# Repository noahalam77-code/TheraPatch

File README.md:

# TheraPatch

## Repository file structure
- BOM: JCLPCB BOM & regular BOM
- CADfiles: STEP files, STL files, and assembly notes
- PCB: PCB files, Gerber files, schematic images, and PCB images
- Firmware: Code & flashing instructions

## What it is
TheraPatch is a handheld therapeutic device designed to help mitigate the effects of injuries such as bruises, sprains, minor cuts, and more. By using a reverse-polarity system via an H-bridge, TheraPatch can heat the affected area (dilating blood vessels) or cool it (constricting blood vessels), both of which have been shown to help with injury healing at certain temperatures (which TheraPatch can achieve). 

## Motivation
I created TheraPatch with the primary motivation of helping people with common sports/activty related injuries while maintaining an efficient device to do so. Most of the time, when you have a bruise or scrape, you'd rely on disposable ice packs or inefficient heating pads, which are wasteful and time-consuming for long-term use. TheraPatch offers an effective, infinitely reusable solution to this. Instead of freezing water for 3-4 hours or boiling a heatpack everytime you need to reuse it, all you do with TheraPatch is plug and play. It's effective for athletes and normal people.

## Use of TheraPatch
To use the TheraPatch, first ensure your battery/wall adapter is plugged in. Then locate the 4 buttons on the top of the device; these buttons will allow you to set your desired parameters by moving through the menus: mode (hot/cold), set temp, and set time. After your desired settings are set, click the start button to initiate your therapy session, and place the side with the Peltier facing out against the affected area

## How it works
The TheraPatch looks like a simple black-and-white hot-cold block, but its guts are far more advanced. In electronics, generating heat is relatively simple. Electrons bump into each other rapidly in the wire, vibrating and thus creating the heat we feel. This is the easy part; cooling is the real engineering challenge. To cool it, I used a Peltier module, which transfers heat from one side to the other. Now, this needs to be driven by a heatsink and a fan to effectively cool. To achieve heating and cooling on the same side, I used an H bridge. The H-bridge module reverses the polarity in a Peltier module, meaning that when one side is positive and the other is negative, it cools; vice versa. All of this is controlled by a custom 4-layer PCB I designed in KiCad, with an ATmega328P as my microcontroller. The firmware reads a thermistor pressed against the Peltier plate and uses a bang-bang controller to turn the Peltier on/off to reach the desired temperature. This is all run by a rechargeable 12V battery, which charges via USB-C or a 12V wall adapter. These components are combined in a logical order in a CAD-designed box with a hole for all the input plugs and vent fans for air circulation.

Here are images of my project

## CAD with the PCB:

## CAD input ports, fins, and Peliter hole

## Link to Onshape case:

https://cad.onshape.com/documents/d627d659f05dae60588ec801/w/ad74ef98cd2d7a13cb59f9ec/e/f50ed022a94792dc2cfe6130?renderMode=0&uiState=6a4947abb17d022f5d41873a

# PCB (Signal Layer and ground):

## F.cu (signal traces and ground):

## In1.cu(ground):

## In2.cu (5V & 12V power)

## B.cu (signal traces and ground):

## 3D:

# Schematic (wiring diagram):

## Pic_1:

## Pwr:

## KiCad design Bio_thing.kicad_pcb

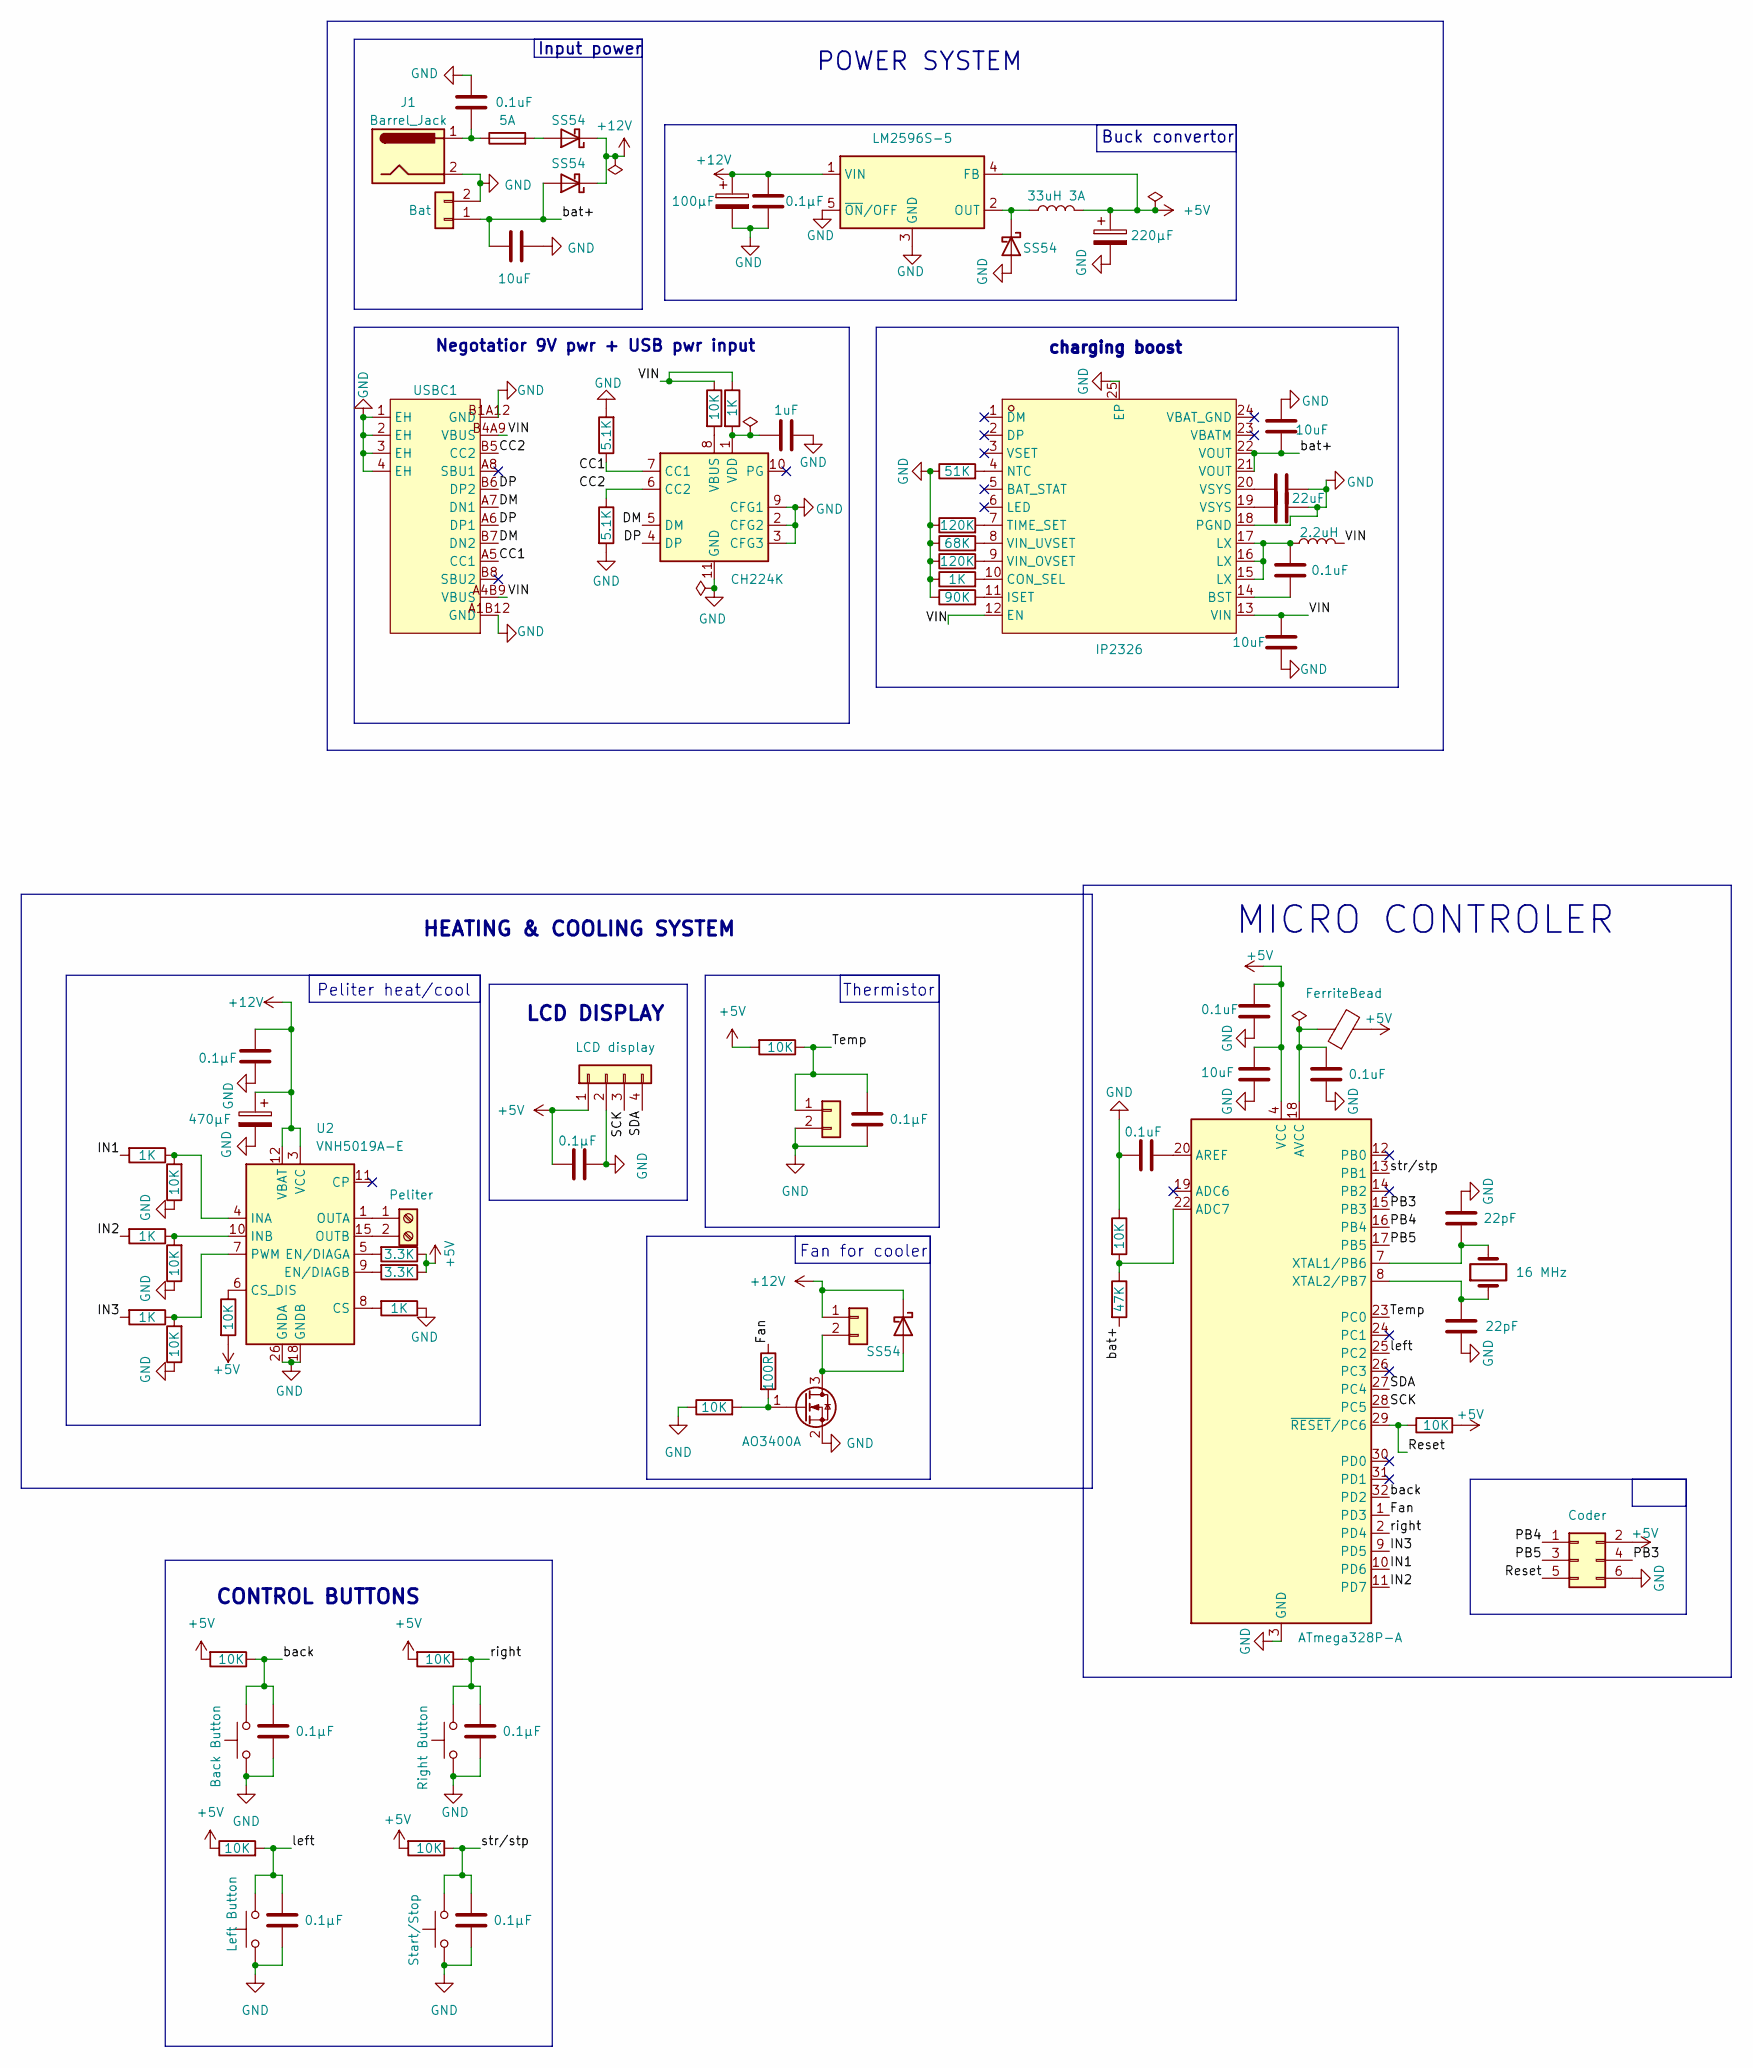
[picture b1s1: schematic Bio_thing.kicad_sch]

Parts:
C1, C3, C4, C5, C6, C9, C12, C15: 0.1µF; C_0603_1608Metric
C2: 220µF; CP_Elec_6.3x7.7
C7: 1uF; C_0603_1608Metric
C8: 100µF; CP_Elec_6.3x7.7
C10, C22, C23, C25: 10uF; C_1206_3216Metric
C11, C13, C18, C19, C24: 0.1uF; C_0603_1608Metric
C14, C17: 22uF; C_0805_2012Metric
C16: 470µF; CP_Elec_10x10.5
C20, C21: 22pF; C_0603_1608Metric
D1, D2, D3, D6: SS54; D_SMA
F2: 5A; Fuse_1206_3216Metric
FB1: FerriteBead; L_0805_2012Metric
J1: Barrel_Jack; Barrel_JJack
J2: Peliter; TerminalBlock_Phoenix_PT-1,5-2-5.0-H_1x02_P5.00mm_Horizontal
J4: Coder; PinHeader_2x03_P2.54mm_Vertical
J5: fan; JST_XH_B2B-XH-A_1x02_P2.50mm_Vertical
J6: LCD display; PinSocket_1x04_P2.54mm_Vertical
J7: Bat; JST_XH_B2B-XH-A_1x02_P2.50mm_Vertical
J9: themrisotorr; JST_XH_B2B-XH-A_1x02_P2.50mm_Vertical
L1: 33uH 3A; IND-SMD_L12.3-W12.3
L2: 2.2uH; L_Sunlord_MWSA0503S
Q4: AO3400A; SOT-23
R1, R2, R3, R5, R8, R9, R10, R12, R13, R16, R28, R33, R34: 10K; R_0805_2012Metric
R4, R6, R15, R17, R23, R32: 1K; R_0603_1608Metric
R7, R14: 3.3K; R_0603_1608Metric
R11: 100R; R_0603_1608Metric
R18, R19: 5.1K; R_0805_2012Metric
R20: 51K; R_0805_2012Metric
R21, R35: 120K; R_0805_2012Metric
R22: 68K; R_0805_2012Metric
R24: 90K; R_0805_2012Metric
R27: 47K; R_0805_2012Metric
SW2: Left Button; SW_PUSH_6mm_H4.3mm
SW3: Start/Stop; SW_PUSH_6mm_H4.3mm
SW4: Back Button; SW_PUSH_6mm_H4.3mm
SW5: Right Button; SW_PUSH_6mm_H4.3mm
U1: LM2596S-5; TO-263-5_TabPin3
U2: VNH5019A-E; ST_MultiPowerSO-30
U3: CH224K; ESSOP-10_L4.9-W3.9-P1.0-LS6.0-TL-EP
U4: ATmega328P-A; TQFP-32_7x7mm_P0.8mm
U5: IP2326; QFN-24-1EP_4x4mm_P0.5mm_EP2.6x2.6mm; MPN IP2326; LCSC Part C2832094
USBC1: TYPE-C-31-M-12; USB-C_SMD-TYPE-C-31-M-12_1; MPN TYPE-C-31-M-12; LCSC Part C165948
Y1: 16 MHz; Crystal_SMD_5032-2Pin_5.0x3.2mm

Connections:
+5V: C2.1, C12.1, C13.1, C22.1, FB1.2, J4.2, J6.1, L1.2, R2.2, R3.2, R5.2, R7.1, R8.2, R9.2, R10.1, R13.2, R14.1, U1.4 (FB), U4.4 (VCC), U4.6 (VCC)
+12V: C8.1, C9.1, C15.1, C16.1, D1.1 (K), D3.1 (K), D6.1 (K), J5.1, U1.1 (VIN), U2.3 (VCC), U2.12 (VBAT), U2.13 (VCC), U2.23 (VCC), U2.31 (VCC)
/CC1: R18.1, U3.7 (CC1), USBC1.A5 (CC1)
/CC2: R19.1, U3.6 (CC2), USBC1.B5 (CC2)
/DM: U3.5 (DM), USBC1.A7 (DN1), USBC1.B7 (DN2)
/DP: U3.4 (DP), USBC1.A6 (DP1), USBC1.B6 (DP2)
/Fan: R11.1, U4.1 (PD3)
/IN1: R17.2, U4.10 (PD6)
/IN2: R32.2, U4.11 (PD7)
/IN3: R15.2, U4.9 (PD5)
/PB3: J4.4, U4.15 (PB3)
/PB4: J4.1, U4.16 (PB4)
/PB5: J4.3, U4.17 (PB5)
/Reset: J4.5, R13.1, U4.29 (~RESET/PC6)
/SCK: J6.3, U4.28 (PC5)
/SDA: J6.4, U4.27 (PC4)
/Temp: C4.1, J9.1, R2.1, U4.23 (PC0)
/VIN: C10.2, L2.2, R6.1, R12.1, U5.12 (EN), U5.13 (VIN), USBC1.A4B9 (VBUS), USBC1.B4A9 (VBUS)
/back: C3.1, R8.1, SW4.2, U4.32 (PD2)
/bat+: C23.1, C25.1, D3.2 (A), J7.1, R27.2, U5.21 (VOUT), U5.22 (VOUT)
/left: C5.1, R10.2, SW2.2, U4.25 (PC2)
/right: C6.1, R9.1, SW5.2, U4.2 (PD4)
/str/stp: C1.1, R3.1, SW3.2, U4.13 (PB1)
GND: C1.2, C2.2, C3.2, C4.2, C5.2, C6.2, C7.2, C8.2, C9.2, C10.1, C12.2, C13.2, C14.2, C15.2, C16.2, C17.2, C18.2, C19.1, C20.2, C21.1, C22.2, C23.2, C24.1, C25.2, D2.2 (A), J1.2, J4.6, J6.2, J7.2, J9.2, Q4.2 (S), R1.1, R4.1, R16.1, R18.2, R19.2, R20.1, R21.1, R22.1, R23.1, R24.1, R28.1, R33.1, R34.1, R35.1, SW2.1, SW3.1, SW4.1, SW5.1, U1.3 (GND), U1.5 (~ON/OFF), U2.18 (GNDB), U2.19 (GNDB), U2.20 (GNDB), U2.26 (GNDA), U2.27 (GNDA), U2.28 (GNDA), U3.2 (CFG2), U3.3 (CFG3), U3.9 (CFG1), U3.11 (GND), U4.3 (GND), U4.5 (GND), U4.21 (GND), U5.18 (PGND), U5.25 (EP), USBC1.1 (EH), USBC1.2 (EH), USBC1.3 (EH), USBC1.4 (EH), USBC1.A1B12 (GND), USBC1.B1A12 (GND)
unnamed: C11.1, L2.1, U5.15 (LX), U5.16 (LX), U5.17 (LX)
unnamed: C14.1, U5.19 (VSYS)
unnamed: C17.1, U5.20 (VSYS)
unnamed: C24.2, F2.1, J1.1
unnamed: D1.2 (A), J5.2, Q4.3 (D)
unnamed: D2.1 (K), L1.1, U1.2 (OUT)
unnamed: D6.2 (A), F2.2
unnamed: J2.1, U2.1 (OUTA), U2.25 (OUTA), U2.30 (OUTA), U2.33 (OUTA)
unnamed: J2.2, U2.15 (OUTB), U2.16 (OUTB), U2.21 (OUTB), U2.32 (OUTB)
unnamed: Q4.1 (G), R1.2, R11.2
unnamed: R4.2, U2.8 (CS)
unnamed: R5.1, U2.6 (CS_DIS)
unnamed: R7.2, U2.5 (EN/DIAGA)
unnamed: R14.2, U2.9 (EN/DIAGB)
unnamed: R17.1, R33.2, U2.4 (INA)
unnamed: R32.1, R34.2, U2.10 (INB)
unnamed: R15.1, R16.2, U2.7 (PWM)
unnamed: R12.2, U3.8 (VBUS)
unnamed: C7.1, R6.2, U3.1 (VDD)
unnamed: R27.1, R28.2, U4.22 (ADC7)
unnamed: C19.2, U4.20 (AREF)
unnamed: C18.1, FB1.1, U4.18 (AVCC)
unnamed: C21.2, U4.7 (XTAL1/PB6), Y1.2
unnamed: C20.1, U4.8 (XTAL2/PB7), Y1.1
unnamed: C11.2, U5.14 (BST)
unnamed: R23.2, U5.10 (CON_SEL)
unnamed: R24.2, U5.11 (ISET)
unnamed: R20.2, U5.4 (NTC)
unnamed: R21.2, U5.7 (TIME_SET)
unnamed: R35.2, U5.9 (VIN_OVSET)
unnamed: R22.2, U5.8 (VIN_UVSET)

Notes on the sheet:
Thermistor
MICRO CONTROLER
Negotatior 9V pwr + USB pwr input
Peliter heat/cool
charging boost
POWER SYSTEM
HEATING & COOLING SYSTEM
LCD DISPLAY
Buck convertor
Input power
Fan for cooler
CONTROL BUTTONS

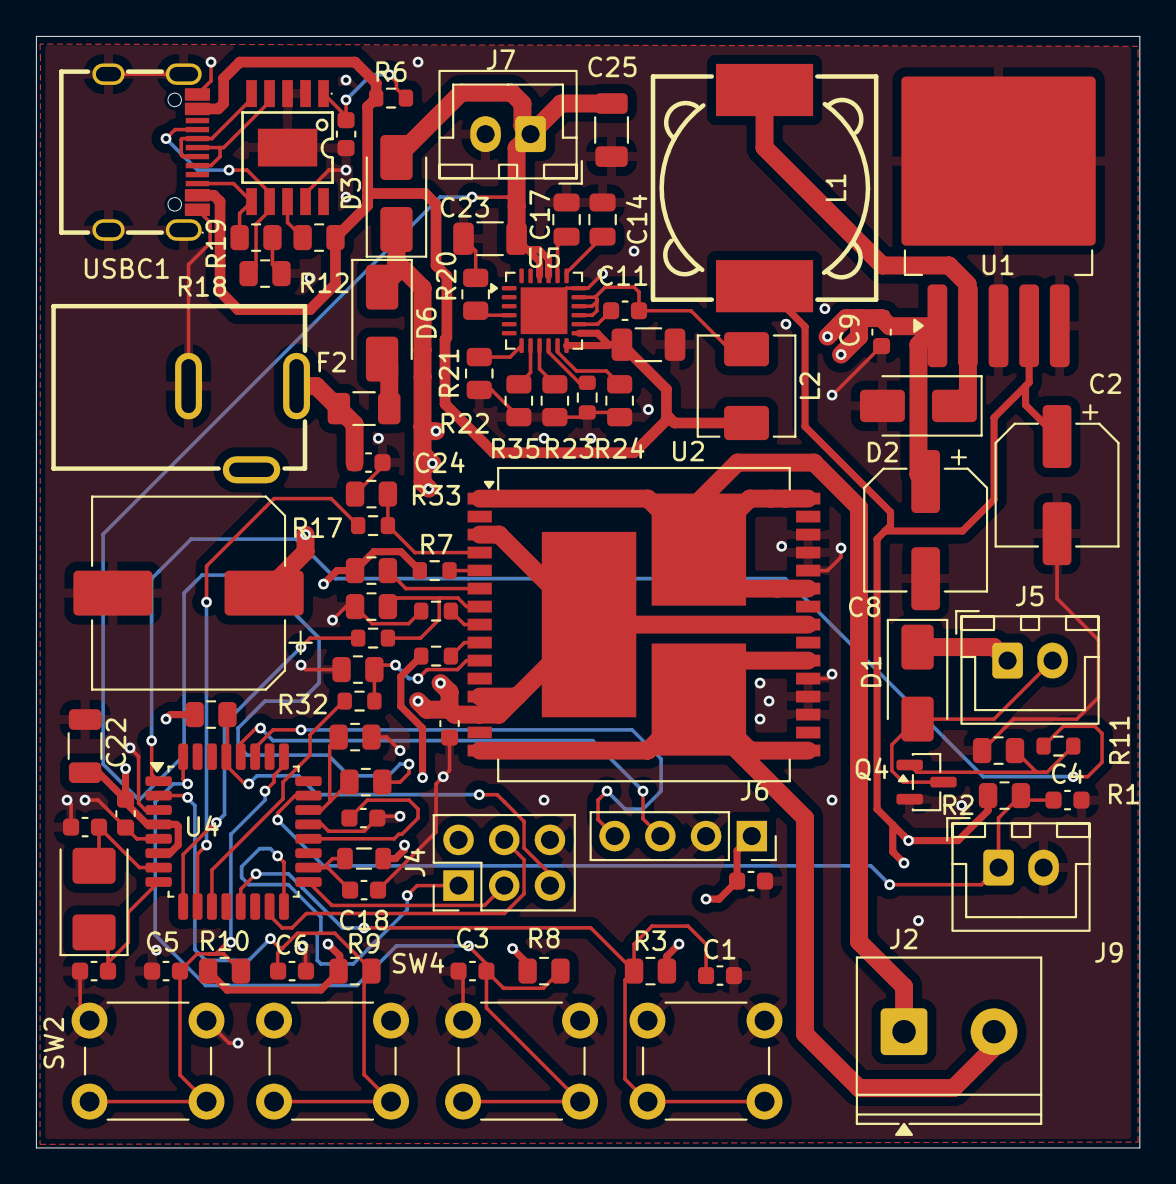
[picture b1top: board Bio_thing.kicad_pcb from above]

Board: 4 copper layers, 61.3 x 61.7 mm, 82 parts (0 on the bottom side), 55 nets.

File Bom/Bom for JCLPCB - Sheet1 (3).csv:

Comment,Designator,Footprint,LCSC Part Number
USB-C,USBC1,USBC_U:USB-C_SMD-TYPE-C-31-M-12_1,C165948
5A Fuse,F2,Fuse:Fuse_1206_3216Metric,C41367229
Crystal,Y1,Crystal:Crystal_SMD_5032-2Pin_5.0x3.2mm,C122519
Ferrite bead,FB1,Inductor_SMD:L_0805_2012Metric,C21519
AO3400A diode,Q4,Package_TO_SOT_SMD:SOT-23,C20917
SS54 Diode,"D1, D2, D3, D6",Diode_SMD:D_SMA,C22452
33µH inductor,L1,inductor_33uh:IND-SMD_L12.3-W12.3,C9400
2.2µH boost Inductor,L2,Inductor_SMD:L_Sunlord_MWSA0503S,C7461347
120K Resitor,"R21, R35",Resistor_SMD:R_0805_2012Metric,C2907223
90K Resitor,R24,Resistor_SMD:R_0805_2012Metric,C5123603
68K Resitor,R22,Resistor_SMD:R_0805_2012Metric,C2907283
51K Resitor,R20,Resistor_SMD:R_0805_2012Metric,C2933461
47K restior,R27,Resistor_SMD:R_0805_2012Metric,C2930202
10K Restior,"R34, R33, R28, R16, R13, R12, R10, R9, R8, R5, R3, R2, R1",Resistor_SMD:R_0805_2012Metric,C2907219
5.1K resistor,"R18, R19",Resistor_SMD:R_0805_2012Metric,C27834
3.3K resistor,"R7, R14",Resistor_SMD:R_0603_1608Metric,C2907023
1k resistor,"R32, R23, R17, R15, R6, R4",Resistor_SMD:R_0603_1608Metric,C22548
100Ω resistor,R11,Resistor_SMD:R_0603_1608Metric,C105588
470uF capacitor,C16,Capacitor_SMD:CP_Elec_10x10.5,C976030
220uF capacitor,C2,Capacitor_SMD:CP_Elec_6.3x7.7,C22388075
100uF capacitor,C8,Capacitor_SMD:CP_Elec_6.3x7.7,C970685
22uF capacitor,"C14, C17",Capacitor_SMD:C_0805_2012Metric,C45783
10uF capacitor,"C25, C23, C22,C10",Capacitor_SMD:C_1206_3216Metric,C9807
1uF capacitor,C7,Capacitor_SMD:C_0603_1608Metric,C29936
0.1uF capacitor,"C24, C19, C18, C15, C13, C12, C11, C9, C6, C5, C4, C3, C1",Capacitor_SMD:C_0603_1608Metric,C1590
22pF capacitor,"C20,C21",Capacitor_SMD:C_0603_1608Metric,C1653
ST VNH5019ATR-E,U2,Package_SO:ST_MultiPowerSO-30,C2653552
LM2596S-5.0,U1,Package_TO_SOT_SMD:TO-263-5_TabPin3,C116713
WCH CH224K,U3,CH224K:ESSOP-10_L4.9-W3.9-P1.0-LS6.0-TL-EP,C970725
IP2326,U5,Package_DFN_QFN:QFN-24-1EP_4x4mm_P0.5mm_EP2.6x2.6mm,C2832094
ATMEGA328P-AU,U4,Package_QFP:TQFP-32_7x7mm_P0.8mm,C14877

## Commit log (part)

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2026-06-01 Create PCB
2026-06-03 Create Schematic
2026-06-08 Rename F.Cu_PCB.png to PCB/F.Cu_PCB.png
2026-06-08 Rename In1.Cu PCB.png to PCB/In1.Cu PCB.png
2026-06-08 Rename In2.Cu_PCB.png to PCB/In2.Cu_PCB.png
2026-06-08 Rename B.Cu_PCB.png to PCB/B.Cu_PCB.png
2026-06-08 Rename Bio_thing.kicad_pcb to PCB/Bio_thing.kicad_pcb
2026-06-29 Refactor firmware by removing unused code and improving control functions
    Removed unused Adafruit display code and related variables. Updated Peltier control functions for better clarity and organization.
